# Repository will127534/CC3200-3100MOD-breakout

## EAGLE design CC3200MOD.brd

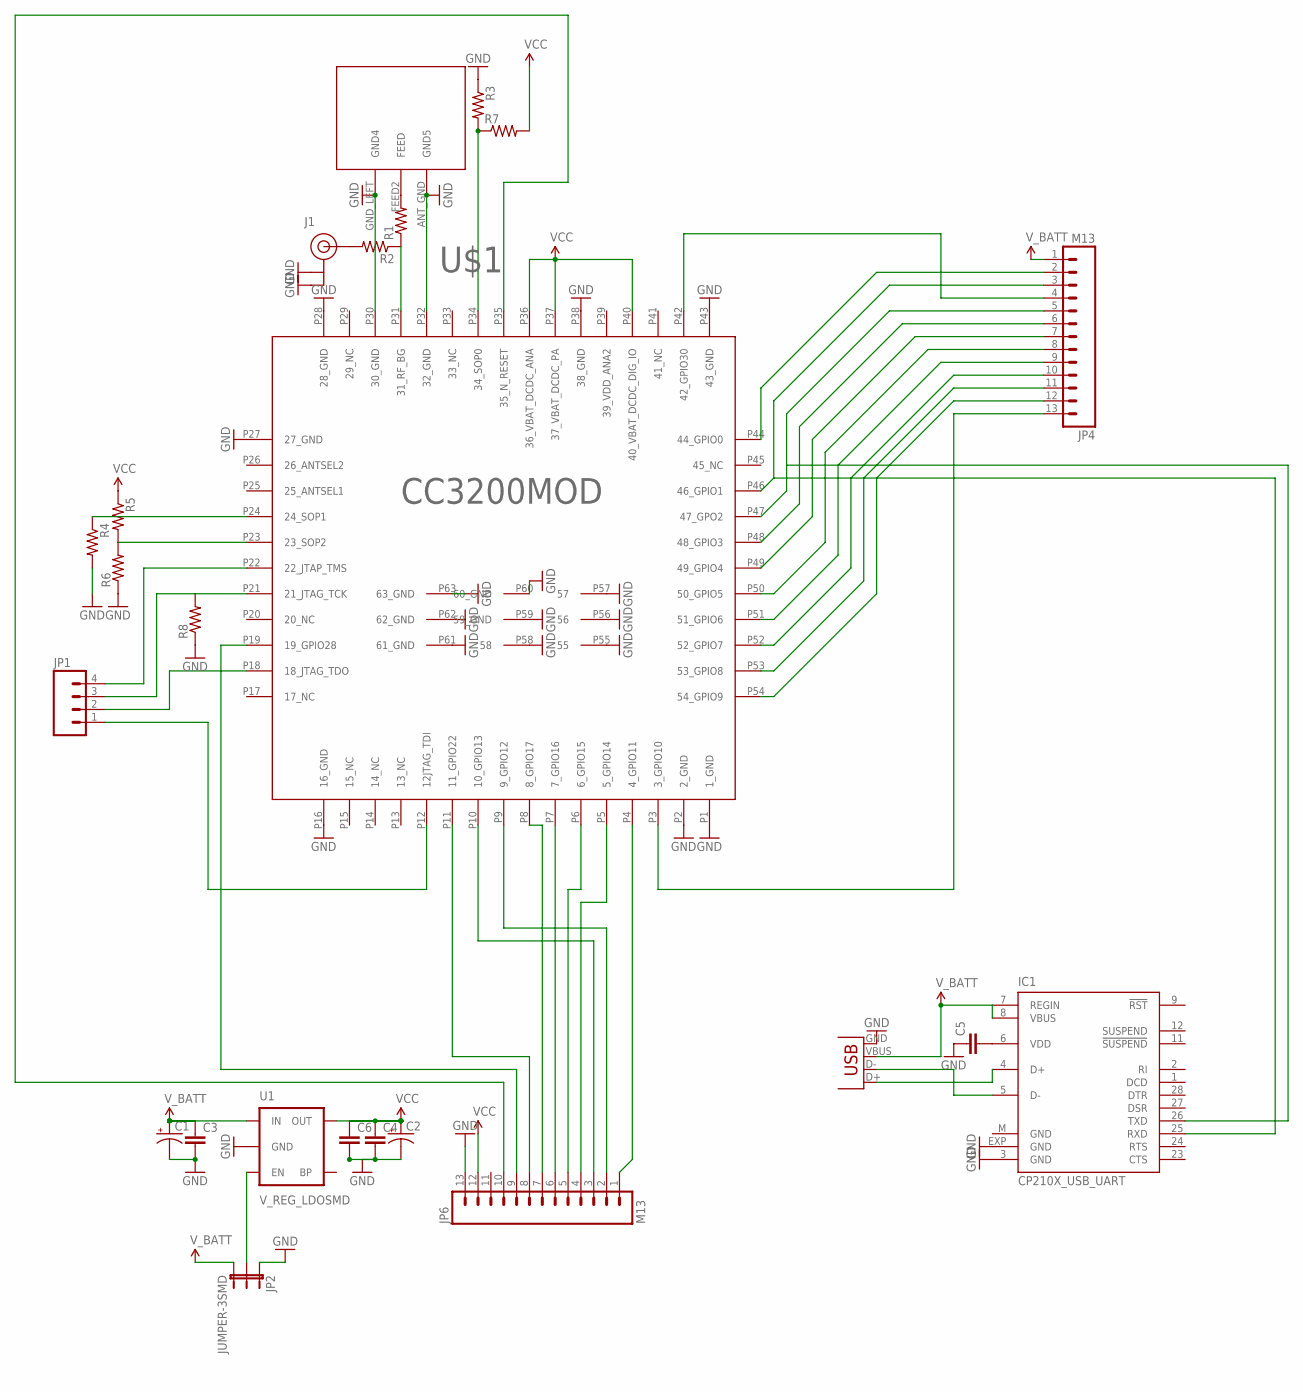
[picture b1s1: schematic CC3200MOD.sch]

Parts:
C1, C2: CAP_POL1206; EIA3216
C3, C4, C5, C6: CAP0805; 0805
IC1: CP210X_USB_UART; MLP28
J1: U.FL
JP1: M041.27MM; 1X04-1.27MM
JP2: JUMPER-3SMD; SJ_3
JP4, JP6: M13; 1X13
JP5: USBSMD; USB-MINIB
R1, R2: R-US_R0402; R0402
R3, R4, R5, R6, R7, R8: RESISTOR0805-RES; 0805
U1: V_REG_LDOSMD; SOT23-5
U$1: CC3200; CC3200MOD
U$2: ANT

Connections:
GND: C1.C (-), C2.C (-), C3.2, C4.2, C5.1, C6.2, IC1.3 (GND), IC1.EXP (GND), IC1.M (GND), J1.P$1 (GND), J1.P$2 (GND), JP2.1, JP5.GND, JP6.13, R3.1, R4.2, R6.1, R8.1, U1.2 (GND), U$1.P1 (1_GND), U$1.P2 (2_GND), U$1.P16 (16_GND), U$1.P27 (27_GND), U$1.P28 (28_GND), U$1.P30 (30_GND), U$1.P32 (32_GND), U$1.P38 (38_GND), U$1.P43 (43_GND), U$1.P55 (55), U$1.P56 (56), U$1.P57 (57), U$1.P58 (58), U$1.P59 (59_GND), U$1.P60 (60_GND), U$1.P61 (61_GND), U$1.P62 (62_GND), U$1.P63 (63_GND), U$2.ANT_GND (GND5), U$2.GND_LEFT (GND4)
unnamed: R1.2, U$2.FEED2 (FEED)
unnamed: JP1.3, R8.2, U$1.P21 (21_JTAG_TCK)
unnamed: JP1.4, U$1.P22 (22_JTAP_TMS)
unnamed: R1.1, R2.1, U$1.P31 (31_RF_BG)
unnamed: J1.P$3 (SIGNAL), R2.2
unnamed: R4.1, U$1.P24 (24_SOP1)
unnamed: JP4.2, U$1.P44 (44_GPIO0)
unnamed: R3.2, R7.1, U$1.P34 (34_SOP0)
unnamed: JP1.2, U$1.P18 (18_JTAG_TDO)
unnamed: JP1.1, U$1.P12 (12JTAG_TDI)
unnamed: R5.2, R6.2, U$1.P23 (23_SOP2)
unnamed: IC1.25 (RXD), JP4.3, U$1.P46 (46_GPIO1)
unnamed: IC1.26 (TXD), JP4.5, U$1.P47 (47_GPO2)
unnamed: JP4.6, U$1.P48 (48_GPIO3)
unnamed: JP4.7, U$1.P49 (49_GPIO4)
unnamed: JP4.8, U$1.P50 (50_GPIO5)
unnamed: JP4.9, U$1.P51 (51_GPIO6)
unnamed: JP4.10, U$1.P52 (52_GPIO7)
unnamed: JP4.11, U$1.P53 (53_GPIO8)
unnamed: JP4.12, U$1.P54 (54_GPIO9)
unnamed: JP4.13, U$1.P3 (3_GPIO10)
unnamed: IC1.4 (D+), JP5.D+
unnamed: JP6.2, U$1.P9 (9_GPIO12)
unnamed: JP2.2, U1.3 (EN)
unnamed: JP4.4, U$1.P42 (42_GPIO30)
unnamed: JP6.4, U$1.P5 (5_GPIO14)
unnamed: JP6.5, U$1.P6 (6_GPIO15)
unnamed: JP6.1, U$1.P4 (4_GPIO11)
unnamed: JP6.6, U$1.P7 (7_GPIO16)
unnamed: IC1.5 (D-), JP5.D-
unnamed: JP6.10, U$1.P35 (35_N_RESET)
unnamed: JP6.9, U$1.P19 (19_GPIO28)
unnamed: JP6.7, U$1.P8 (8_GPIO17)
unnamed: JP6.8, U$1.P11 (11_GPIO22)
unnamed: C5.2, IC1.6 (VDD)
unnamed: JP6.3, U$1.P10 (10_GPIO13)
VCC: C2.A (+), C4.1, C6.1, JP6.12, R5.1, R7.2, U1.5 (OUT), U$1.P36 (36_VBAT_DCDC_ANA), U$1.P37 (37_VBAT_DCDC_PA), U$1.P40 (40_VBAT_DCDC_DIG_IO)
V_BATT: C1.A (+), C3.1, IC1.7 (REGIN), IC1.8 (VBUS), JP2.3, JP4.1, JP5.VBUS, U1.1 (IN)

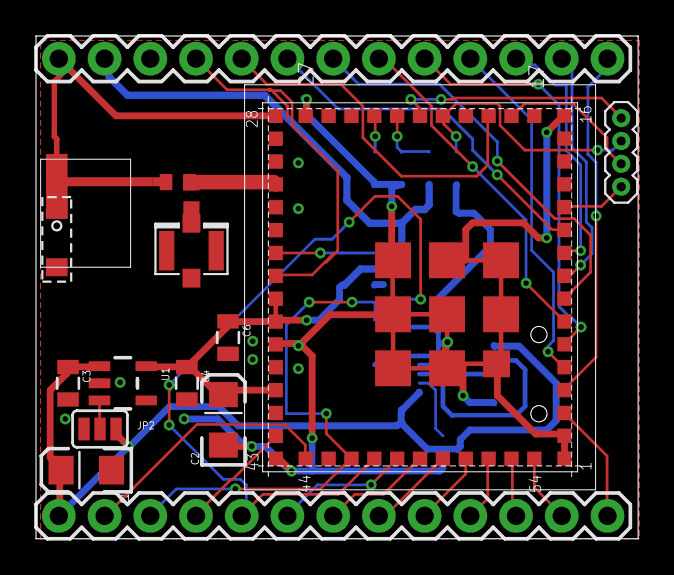
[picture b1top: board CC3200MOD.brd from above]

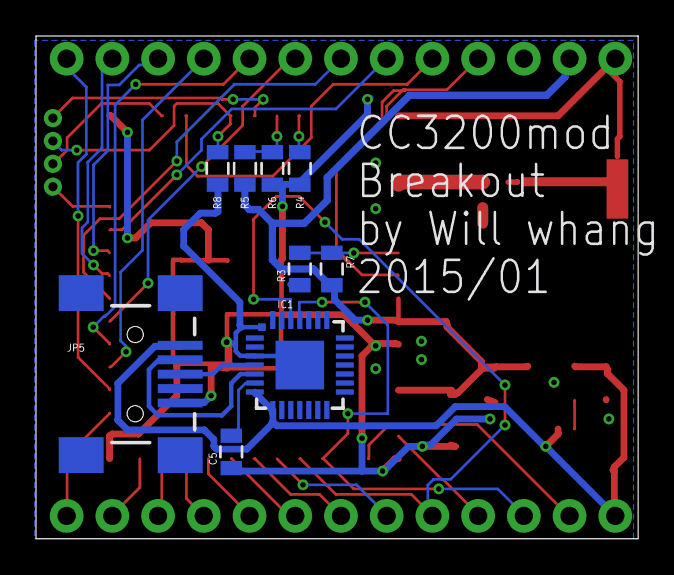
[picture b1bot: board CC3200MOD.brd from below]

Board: 2 copper layers, 33.5 x 27.9 mm, 24 parts (9 on the bottom side), 39 nets.

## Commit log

2015-02-09 :tada: Added .gitattributes & .gitignore files
2015-02-09 Ver 1.0

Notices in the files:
parts and their libraries:
SparkFun-Connectors: Licensing: CC v3.0 Share-Alike You are welcome to use this library for commercial purposes.
